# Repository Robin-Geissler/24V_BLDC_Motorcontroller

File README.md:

# 24V BLDC Motorcontroller

This is a motorcontroller to control a 24V BLDC motor. In this project the controller was used to control a Faulhaber 4221 BXT R to power a 2DOF robot. The 6 Step control algorithm is used to control the motor. The motorcontroller implements the following control modes:
* Current Control
* Speed Control
* Position Control
* Torque Control

## Control Structure
A current controller and a speed controller are used as low level controllers for the position and torque controller. Each controlmode can be accessed by the user.

**Current Control** 
Uses currentsensors on the PCB to control the motor current. 

**Speed Control** 
Calculates the speed by analysing the HAL Sector change rate. 

**Position Control**
The position of the geaboxshaft is measured with an AksIM-2 absolute encoder from RLS. The control structure of the position controller looks like this:

**Torque Control**
The torque applied to the gearbox shaft is measured with a TS70a torque sensor from ME-Meßsysteme. The control structure of the torque controller looks like this:

## Comunication Interface
The controller provides an EtherCAT communication interface. Over the interface the controlmode can be set, and PID controlparameters for each controller can be manipulated.

## Hardware
A Microchip ATSAMD51G19A is used as an MCU. It controls a MP6540HA motordriver IC.

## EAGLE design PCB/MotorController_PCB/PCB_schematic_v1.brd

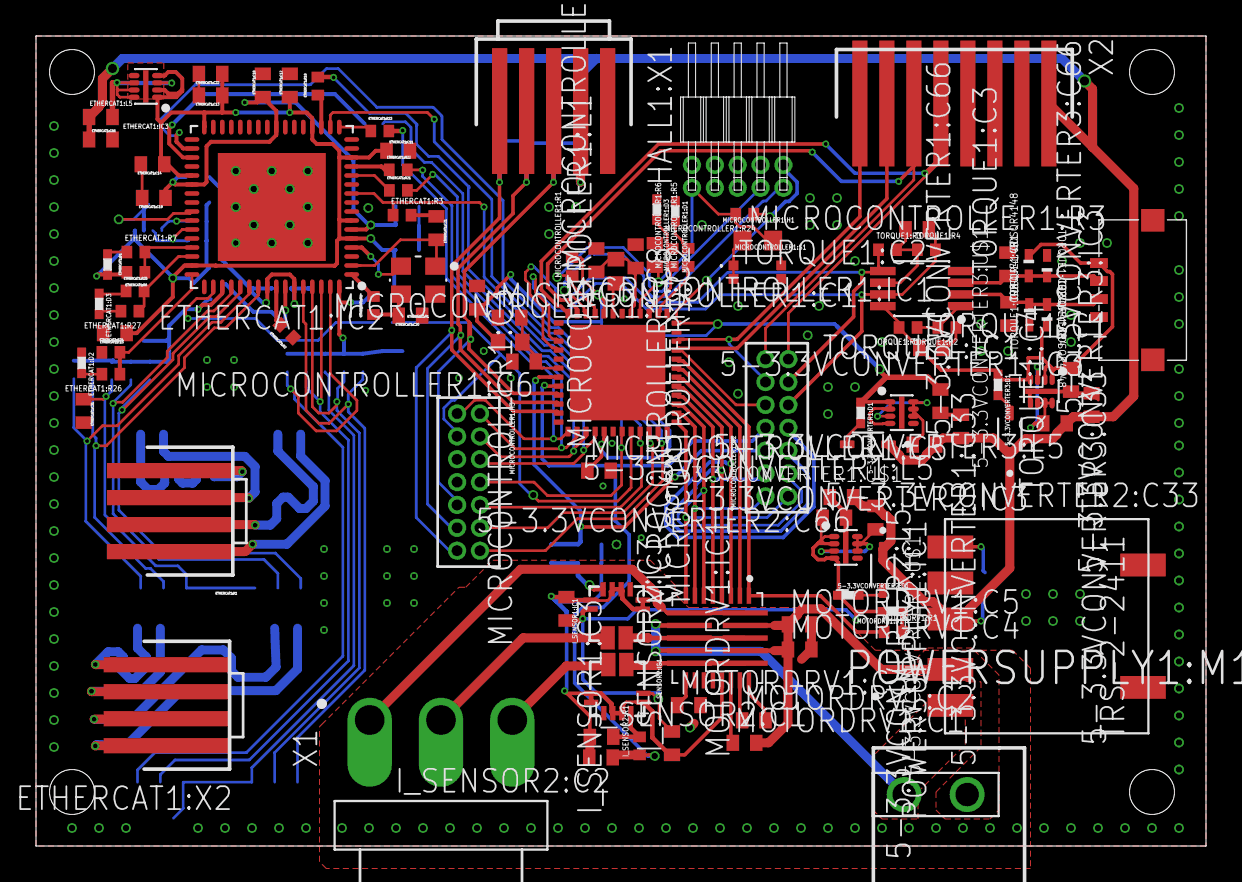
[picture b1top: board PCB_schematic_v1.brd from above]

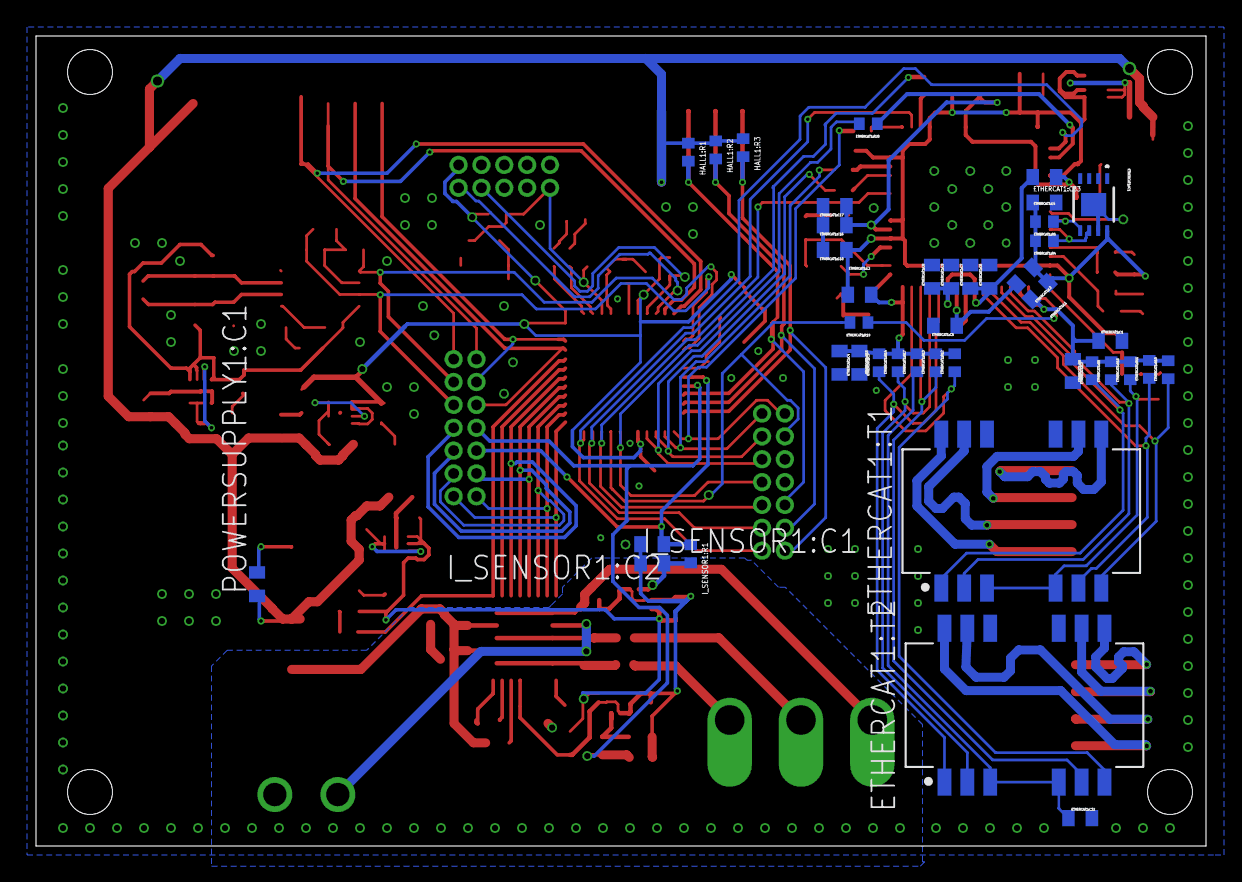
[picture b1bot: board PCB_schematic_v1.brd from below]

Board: 2 copper layers, 65.0 x 45.0 mm, 150 parts (42 on the bottom side), 111 nets.

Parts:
5-3.3VCONVERTER1:C33, 5-3.3VCONVERTER2:C33, 5-3.3VCONVERTER3:C33: GRM155C80J106ME11D; C0402
5-3.3VCONVERTER1:C66, 5-3.3VCONVERTER2:C66, 5-3.3VCONVERTER3:C66: GCM155C71A105KE38D; C0402
5-3.3VCONVERTER1:D1, 5-3.3VCONVERTER2:D1, 5-3.3VCONVERTER3:D1: QBLP595-R; LED0402
5-3.3VCONVERTER1:IC3, 5-3.3VCONVERTER2:IC3, 5-3.3VCONVERTER3:IC3: RP115L331D-E2; SON40P120X160X40-9T30X130N
5-3.3VCONVERTER1:L5, 5-3.3VCONVERTER2:L5, 5-3.3VCONVERTER3:L5: BLM15EG221SH1D; BEAD0402
5-3.3VCONVERTER1:U$1, 5-3.3VCONVERTER2:U$1, 5-3.3VCONVERTER3:U$1: MM3Z3V0B; SODFL2513X100N
ETHERCAT1:C1, ETHERCAT1:C3, ETHERCAT1:C66: GCM155C71A105KE38D; C0402
ETHERCAT1:C2, ETHERCAT1:C4, ETHERCAT1:C5, ETHERCAT1:C7, ETHERCAT1:C9, ETHERCAT1:C10, ETHERCAT1:C11, ETHERCAT1:C12, ETHERCAT1:C13, ETHERCAT1:C14, ETHERCAT1:C15, ETHERCAT1:C18, ETHERCAT1:C19, ETHERCAT1:C22: 100n; C0402
ETHERCAT1:C6, ETHERCAT1:C8, ETHERCAT1:C16: 1u; C0402
ETHERCAT1:C17: 470p; C0402
ETHERCAT1:C20, ETHERCAT1:C21: 18p; C0402
ETHERCAT1:C31, ETHERCAT1:C32: 22n; C0402
ETHERCAT1:C33: GRM155C80J106ME11D; C0402
ETHERCAT1:D1: QBLP595-IG; LED0402
ETHERCAT1:D2: QBLP595-IB; LED0402
ETHERCAT1:D3: QBLP595-O; LED0402
ETHERCAT1:IC1: CAT24C512IGT3HU5; UDFN8
ETHERCAT1:IC2: LAN9253-I/R4X; QFN64-T600
ETHERCAT1:IC3: RP115L331D-E2; SON40P120X160X40-9T30X130N
ETHERCAT1:L1, ETHERCAT1:L2, ETHERCAT1:L3, ETHERCAT1:L4, ETHERCAT1:L5: BLM15EG221SH1D; BEAD0402
ETHERCAT1:R1, ETHERCAT1:R16, ETHERCAT1:R17: RT0402FRE070RL; R0402
ETHERCAT1:R2: 12k1; R0402
ETHERCAT1:R3, ETHERCAT1:R7, ETHERCAT1:R26, ETHERCAT1:R27: RL1206FR-7WL; R0402
ETHERCAT1:R4, ETHERCAT1:R5: 4k7; R0402
ETHERCAT1:R6, ETHERCAT1:R24, ETHERCAT1:R25: 10k; R0402
ETHERCAT1:R8, ETHERCAT1:R9, ETHERCAT1:R10, ETHERCAT1:R11, ETHERCAT1:R12, ETHERCAT1:R13, ETHERCAT1:R14, ETHERCAT1:R15: 49R9; R0402
ETHERCAT1:R18, ETHERCAT1:R19, ETHERCAT1:R20, ETHERCAT1:R21, ETHERCAT1:R22, ETHERCAT1:R23: 100; R0402
ETHERCAT1:T1, ETHERCAT1:T2: 749020100; SOIC127P965X533-16-TRAFO
ETHERCAT1:X1, ETHERCAT1:X2: 87438-0443; 87438-04
ETHERCAT1:Y1: ECX-2236
HALL1:R1, HALL1:R2, HALL1:R3: RT0402BRD0710KL; R0402
HALL1:X1: 87438-0543; 87438-05
I_SENSOR1:C1, I_SENSOR2:C1: GCM155R71E103KA37; C0402
I_SENSOR1:C2, I_SENSOR1:C3, I_SENSOR2:C2, I_SENSOR2:C3: GCM155R71C104JA55; C0402
I_SENSOR1:IC1, I_SENSOR2:IC1: ACS70331EESATR-005B3; QFN12-ES
I_SENSOR1:R1, I_SENSOR2:R1: RT0402FRE07100RL; R0402
MICROCONTROLLER1:C1, MICROCONTROLLER1:C3: GRM155C80J106ME11D; C0402
MICROCONTROLLER1:C2, MICROCONTROLLER1:C5, MICROCONTROLLER1:C6, MICROCONTROLLER1:C7: GCM155R71C104JA55; C0402
MICROCONTROLLER1:C8: GRM155C80J475MEAAD; C0402
MICROCONTROLLER1:D1, MICROCONTROLLER1:D3: QBLP595-AG; LED0402
MICROCONTROLLER1:H1: 20021112-00010T4LF; 20021112-00010
MICROCONTROLLER1:H2, MICROCONTROLLER1:H3: 20021111-00014T1LF; 20021111-00014
MICROCONTROLLER1:IC1: ATSAMD51G19A-MUT; QFN48
MICROCONTROLLER1:L1, MICROCONTROLLER1:L2: BLM18EG601SN1D; BEADC1608X80
MICROCONTROLLER1:R1: RT0402FRE071KL; R0402
MICROCONTROLLER1:R3: RT0603FRE07330RL; R0603
MICROCONTROLLER1:R5, MICROCONTROLLER1:R6, MICROCONTROLLER1:R24: 10k; R0402
MICROCONTROLLER1:S1: USLPT2616CT2TR; USLPT2616CT
MOTORDRV1:C1: GRM155R6YA105KE11D; C0402
MOTORDRV1:C2, MOTORDRV1:C4, MOTORDRV1:C5: GRM155R62A104KE14; C0402
MOTORDRV1:C3: GRM155R61H472KA01D; C0402
MOTORDRV1:D1: QBLP595-R; LED0402
MOTORDRV1:IC1: MP6540HGUP
MOTORDRV1:R1: RT0402BRD0710KL; R0402
POWERSUPPLY1:C1: GRM155R6YA105KE11D; C0402
POWERSUPPLY1:IC1: TRS-2-2411; 7-SMD
POWERSUPPLY1:M1: PST1,3/2-3,5; 1945096
POWERSUPPLY1:U$1: PTDA1,5/2-PH-3,5; 1725107
TORQUE1:C1: GCM155R71C104JA55; C0402
TORQUE1:C2, TORQUE1:C3, TORQUE1:C4: GCM155R71E103KA37; C0402
TORQUE1:CR1, TORQUE1:CR2, TORQUE1:CR3, TORQUE1:CR4: CDSQR4148; 0402/SOD-923F
TORQUE1:IC1: MAX4208AUA+T; USOP8
TORQUE1:R1, TORQUE1:R2: RT0402FRE0710KL; R0402
TORQUE1:R3: RT0402FRE07150RL; R0402
TORQUE1:R4: RT0402FRE07100KL; R0402
TORQUE1:X3: 5037630491
X1: B3PS-VH(LF)(SN)
X2: 87438-0843; 87438-08

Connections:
5-3.3VCONVERTER1:N$1: 5-3.3VCONVERTER1:D1.2, 5-3.3VCONVERTER1:U$1.A
5-3.3VCONVERTER1:VDD: 5-3.3VCONVERTER1:IC3.3, 5-3.3VCONVERTER1:IC3.6, 5-3.3VCONVERTER1:IC3.7, 5-3.3VCONVERTER1:IC3.8, 5-3.3VCONVERTER1:L5.2
5-3.3VCONVERTER2:N$1: 5-3.3VCONVERTER2:D1.2, 5-3.3VCONVERTER2:U$1.A
5-3.3VCONVERTER2:VDD: 5-3.3VCONVERTER2:IC3.3, 5-3.3VCONVERTER2:IC3.6, 5-3.3VCONVERTER2:IC3.7, 5-3.3VCONVERTER2:IC3.8, 5-3.3VCONVERTER2:L5.2
5-3.3VCONVERTER3:N$1: 5-3.3VCONVERTER3:D1.2, 5-3.3VCONVERTER3:U$1.A
5-3.3VCONVERTER3:VDD: 5-3.3VCONVERTER3:IC3.3, 5-3.3VCONVERTER3:IC3.6, 5-3.3VCONVERTER3:IC3.7, 5-3.3VCONVERTER3:IC3.8, 5-3.3VCONVERTER3:L5.2
+3V3_MD: 5-3.3VCONVERTER2:C33.1, 5-3.3VCONVERTER2:D1.1, 5-3.3VCONVERTER2:IC3.1, 5-3.3VCONVERTER2:IC3.2, 5-3.3VCONVERTER2:IC3.4, I_SENSOR1:C3.2, I_SENSOR1:IC1.12, I_SENSOR2:C3.2, I_SENSOR2:IC1.12, MOTORDRV1:D1.2
+3V3_TS: 5-3.3VCONVERTER3:C33.1, 5-3.3VCONVERTER3:D1.1, 5-3.3VCONVERTER3:IC3.1, 5-3.3VCONVERTER3:IC3.2, 5-3.3VCONVERTER3:IC3.4, TORQUE1:C1.1, TORQUE1:CR1.2, TORQUE1:CR4.2, TORQUE1:IC1.8, TORQUE1:R1.2, TORQUE1:X3.4
+3V3_UC: 5-3.3VCONVERTER1:C33.1, 5-3.3VCONVERTER1:D1.1, 5-3.3VCONVERTER1:IC3.1, 5-3.3VCONVERTER1:IC3.2, 5-3.3VCONVERTER1:IC3.4, MICROCONTROLLER1:C3.2, MICROCONTROLLER1:C5.1, MICROCONTROLLER1:H1.1, MICROCONTROLLER1:IC1.17, MICROCONTROLLER1:IC1.36, MICROCONTROLLER1:IC1.44, MICROCONTROLLER1:L2.1, MICROCONTROLLER1:R1.2, MICROCONTROLLER1:R24.1
+5V: 5-3.3VCONVERTER1:C66.1, 5-3.3VCONVERTER1:L5.1, 5-3.3VCONVERTER1:U$1.C, 5-3.3VCONVERTER2:C66.1, 5-3.3VCONVERTER2:L5.1, 5-3.3VCONVERTER2:U$1.C, 5-3.3VCONVERTER3:C66.1, 5-3.3VCONVERTER3:L5.1, 5-3.3VCONVERTER3:U$1.C, ETHERCAT1:C66.1, ETHERCAT1:L5.1, HALL1:R1.1, HALL1:R2.1, HALL1:R3.1, HALL1:X1.2, POWERSUPPLY1:C1.1, POWERSUPPLY1:IC1.3, X2.1
+24V: MOTORDRV1:C1.2, MOTORDRV1:C4.1, MOTORDRV1:C5.1, MOTORDRV1:IC1.23, MOTORDRV1:IC1.25, POWERSUPPLY1:IC1.2, POWERSUPPLY1:M1.2
ADC_TS: MICROCONTROLLER1:H2.9, MICROCONTROLLER1:IC1.3, TORQUE1:C2.1, TORQUE1:IC1.7, TORQUE1:R4.2
AGND: MOTORDRV1:C3.2, MOTORDRV1:C4.2, MOTORDRV1:C5.2, MOTORDRV1:IC1.10, MOTORDRV1:IC1.12, POWERSUPPLY1:IC1.1, POWERSUPPLY1:M1.1
ENA: MICROCONTROLLER1:H2.7, MICROCONTROLLER1:IC1.30, MOTORDRV1:IC1.3
ENB: MICROCONTROLLER1:H2.5, MICROCONTROLLER1:IC1.29, MOTORDRV1:IC1.4
ENC: MICROCONTROLLER1:H2.4, MICROCONTROLLER1:IC1.28, MOTORDRV1:IC1.5
ENCODER_SPI_MISO: MICROCONTROLLER1:H2.10, MICROCONTROLLER1:IC1.33, X2.7
ENCODER_SPI_MOSI: MICROCONTROLLER1:H2.12, MICROCONTROLLER1:IC1.34, X2.8
ENCODER_SPI_NCS: MICROCONTROLLER1:H2.14, MICROCONTROLLER1:IC1.47, X2.6
ENCODER_SPI_SCK: MICROCONTROLLER1:H2.13, MICROCONTROLLER1:IC1.48, X2.5
ETHERCAT1:#MISO: ETHERCAT1:IC2.13, ETHERCAT1:R22.1
ETHERCAT1:#MOSI: ETHERCAT1:IC2.17, ETHERCAT1:R23.1
ETHERCAT1:#SCK: ETHERCAT1:IC2.19, ETHERCAT1:R18.1
ETHERCAT1:#SCS#: ETHERCAT1:IC2.50, ETHERCAT1:R19.1
ETHERCAT1:#SQI2: ETHERCAT1:IC2.12, ETHERCAT1:R21.1
ETHERCAT1:#SQI3: ETHERCAT1:IC2.35, ETHERCAT1:R20.1
ETHERCAT1:+3V3: ETHERCAT1:C10.1, ETHERCAT1:C11.1, ETHERCAT1:C12.1, ETHERCAT1:C13.1, ETHERCAT1:C14.1, ETHERCAT1:C15.1, ETHERCAT1:C22.1, ETHERCAT1:C33.1, ETHERCAT1:D1.2, ETHERCAT1:IC1.8, ETHERCAT1:IC2.5, ETHERCAT1:IC2.7, ETHERCAT1:IC2.14, ETHERCAT1:IC2.20, ETHERCAT1:IC2.32, ETHERCAT1:IC2.37, ETHERCAT1:IC2.47, ETHERCAT1:IC3.1, ETHERCAT1:IC3.2, ETHERCAT1:IC3.4, ETHERCAT1:L1.1, ETHERCAT1:L2.1, ETHERCAT1:L3.1, ETHERCAT1:R4.2, ETHERCAT1:R5.2, ETHERCAT1:R6.2
ETHERCAT1:CT1: ETHERCAT1:C31.1, ETHERCAT1:R16.1, ETHERCAT1:T1.3, ETHERCAT1:T1.6
ETHERCAT1:CT2: ETHERCAT1:C32.1, ETHERCAT1:R17.1, ETHERCAT1:T2.3, ETHERCAT1:T2.6
ETHERCAT1:GPIO0: ETHERCAT1:IC2.48, ETHERCAT1:R24.2, ETHERCAT1:R26.1
ETHERCAT1:GPIO1: ETHERCAT1:IC2.46, ETHERCAT1:R25.2, ETHERCAT1:R27.1
ETHERCAT1:GPIO2: ETHERCAT1:IC2.45, ETHERCAT1:R6.1, ETHERCAT1:R7.2
ETHERCAT1:I2C_SCL: ETHERCAT1:IC1.6, ETHERCAT1:IC2.43, ETHERCAT1:R4.1
ETHERCAT1:I2C_SDA: ETHERCAT1:IC1.5, ETHERCAT1:IC2.42, ETHERCAT1:R5.1
ETHERCAT1:IN_RX_N: ETHERCAT1:T1.9, ETHERCAT1:X1.4
ETHERCAT1:IN_RX_P: ETHERCAT1:T1.10, ETHERCAT1:X1.3
ETHERCAT1:IN_TX_N: ETHERCAT1:T1.15, ETHERCAT1:X1.2
ETHERCAT1:IN_TX_P: ETHERCAT1:T1.16, ETHERCAT1:X1.1
ETHERCAT1:N$1: ETHERCAT1:D2.2, ETHERCAT1:R26.2
ETHERCAT1:N$2: ETHERCAT1:D3.2, ETHERCAT1:R27.2
ETHERCAT1:N$3: ETHERCAT1:IC3.3, ETHERCAT1:IC3.6, ETHERCAT1:IC3.7, ETHERCAT1:IC3.8, ETHERCAT1:L5.2
ETHERCAT1:N$15: ETHERCAT1:D1.1, ETHERCAT1:R7.1
ETHERCAT1:OSCI: ETHERCAT1:IC2.1, ETHERCAT1:R1.2
ETHERCAT1:OSCI1: ETHERCAT1:C20.2, ETHERCAT1:R1.1, ETHERCAT1:Y1.3
ETHERCAT1:OSCO: ETHERCAT1:C21.2, ETHERCAT1:IC2.2, ETHERCAT1:Y1.1
ETHERCAT1:OUT_RX_N: ETHERCAT1:T2.9, ETHERCAT1:X2.4
ETHERCAT1:OUT_RX_P: ETHERCAT1:T2.10, ETHERCAT1:X2.3
ETHERCAT1:OUT_TX_N: ETHERCAT1:T2.15, ETHERCAT1:X2.2
ETHERCAT1:OUT_TX_P: ETHERCAT1:T2.16, ETHERCAT1:X2.1
ETHERCAT1:RBIAS: ETHERCAT1:IC2.57, ETHERCAT1:R2.2
ETHERCAT1:RXA_N: ETHERCAT1:IC2.54, ETHERCAT1:R10.1, ETHERCAT1:T1.8
ETHERCAT1:RXA_P: ETHERCAT1:IC2.55, ETHERCAT1:R11.1, ETHERCAT1:T1.7
ETHERCAT1:RXB_N: ETHERCAT1:IC2.61, ETHERCAT1:R14.1, ETHERCAT1:T2.2
ETHERCAT1:RXB_P: ETHERCAT1:IC2.60, ETHERCAT1:R15.1, ETHERCAT1:T2.1
ETHERCAT1:TXA_N: ETHERCAT1:IC2.52, ETHERCAT1:R8.1, ETHERCAT1:T1.2
ETHERCAT1:TXA_P: ETHERCAT1:IC2.53, ETHERCAT1:R9.1, ETHERCAT1:T1.1
ETHERCAT1:TXB_N: ETHERCAT1:IC2.63, ETHERCAT1:R12.1, ETHERCAT1:T2.8
ETHERCAT1:TXB_P: ETHERCAT1:IC2.62, ETHERCAT1:R13.1, ETHERCAT1:T2.7
ETHERCAT1:VDD: ETHERCAT1:C16.1, ETHERCAT1:C17.1, ETHERCAT1:C18.1, ETHERCAT1:C19.1, ETHERCAT1:IC2.6, ETHERCAT1:IC2.24, ETHERCAT1:IC2.38, ETHERCAT1:L4.1
ETHERCAT1:VDD12TX: ETHERCAT1:C6.1, ETHERCAT1:C7.1, ETHERCAT1:C8.1, ETHERCAT1:C9.1, ETHERCAT1:IC2.56, ETHERCAT1:IC2.59, ETHERCAT1:L4.2
ETHERCAT1:VDD33BIAS: ETHERCAT1:C5.1, ETHERCAT1:IC2.58, ETHERCAT1:L3.2
ETHERCAT1:VDD33TXRX1: ETHERCAT1:C1.1, ETHERCAT1:C2.1, ETHERCAT1:IC2.51, ETHERCAT1:L1.2, ETHERCAT1:R8.2, ETHERCAT1:R9.2, ETHERCAT1:R10.2, ETHERCAT1:R11.2, ETHERCAT1:R16.2
ETHERCAT1:VDD33TXRX2: ETHERCAT1:C3.1, ETHERCAT1:C4.1, ETHERCAT1:IC2.64, ETHERCAT1:L2.2, ETHERCAT1:R12.2, ETHERCAT1:R13.2, ETHERCAT1:R14.2, ETHERCAT1:R15.2, ETHERCAT1:R17.2
ETH_CS: ETHERCAT1:R19.2, MICROCONTROLLER1:H3.3, MICROCONTROLLER1:IC1.20
ETH_IO2: ETHERCAT1:R21.2, MICROCONTROLLER1:H3.4, MICROCONTROLLER1:IC1.15
ETH_IO3: ETHERCAT1:R20.2, MICROCONTROLLER1:H3.6, MICROCONTROLLER1:IC1.16
ETH_MISO: ETHERCAT1:R22.2, MICROCONTROLLER1:H3.2, MICROCONTROLLER1:IC1.14
ETH_MOSI: ETHERCAT1:R23.2, MICROCONTROLLER1:H3.1, MICROCONTROLLER1:IC1.13
ETH_SCK: ETHERCAT1:R18.2, MICROCONTROLLER1:H3.8, MICROCONTROLLER1:IC1.19
GND: 5-3.3VCONVERTER1:C33.2, 5-3.3VCONVERTER1:C66.2, 5-3.3VCONVERTER1:IC3.5, 5-3.3VCONVERTER1:IC3.9, 5-3.3VCONVERTER2:C33.2, 5-3.3VCONVERTER2:C66.2, 5-3.3VCONVERTER2:IC3.5, 5-3.3VCONVERTER2:IC3.9, 5-3.3VCONVERTER3:C33.2, 5-3.3VCONVERTER3:C66.2, 5-3.3VCONVERTER3:IC3.5, 5-3.3VCONVERTER3:IC3.9, ETHERCAT1:C1.2, ETHERCAT1:C2.2, ETHERCAT1:C3.2, ETHERCAT1:C4.2, ETHERCAT1:C5.2, ETHERCAT1:C6.2, ETHERCAT1:C7.2, ETHERCAT1:C8.2, ETHERCAT1:C9.2, ETHERCAT1:C10.2, ETHERCAT1:C11.2, ETHERCAT1:C12.2, ETHERCAT1:C13.2, ETHERCAT1:C14.2, ETHERCAT1:C15.2, ETHERCAT1:C16.2, ETHERCAT1:C17.2, ETHERCAT1:C18.2, ETHERCAT1:C19.2, ETHERCAT1:C20.1, ETHERCAT1:C21.1, ETHERCAT1:C22.2, ETHERCAT1:C31.2, ETHERCAT1:C32.2, ETHERCAT1:C33.2, ETHERCAT1:C66.2, ETHERCAT1:D2.1, ETHERCAT1:D3.1, ETHERCAT1:IC1.1, ETHERCAT1:IC1.2, ETHERCAT1:IC1.3, ETHERCAT1:IC1.4, ETHERCAT1:IC1.7, ETHERCAT1:IC1.9, ETHERCAT1:IC2.4, ETHERCAT1:IC2.8, ETHERCAT1:IC2.9, ETHERCAT1:IC2.41, ETHERCAT1:IC2.65, ETHERCAT1:IC3.5, ETHERCAT1:IC3.9, ETHERCAT1:R2.1, ETHERCAT1:R3.2, ETHERCAT1:R24.1, ETHERCAT1:R25.1, ETHERCAT1:Y1.2, ETHERCAT1:Y1.4, HALL1:X1.1, I_SENSOR1:C1.1, I_SENSOR1:C2.2, I_SENSOR1:C3.1, I_SENSOR1:IC1.5, I_SENSOR1:IC1.6, I_SENSOR1:IC1.8, I_SENSOR1:IC1.9, I_SENSOR1:IC1.11, I_SENSOR2:C1.1, I_SENSOR2:C2.2, I_SENSOR2:C3.1, I_SENSOR2:IC1.5, I_SENSOR2:IC1.6, I_SENSOR2:IC1.8, I_SENSOR2:IC1.9, I_SENSOR2:IC1.11, MICROCONTROLLER1:C1.1, MICROCONTROLLER1:C2.1, MICROCONTROLLER1:C3.1, MICROCONTROLLER1:C5.2, MICROCONTROLLER1:C6.2, MICROCONTROLLER1:C7.2, MICROCONTROLLER1:C8.1, MICROCONTROLLER1:D1.1, MICROCONTROLLER1:D3.1, MICROCONTROLLER1:H1.3, MICROCONTROLLER1:H1.5, MICROCONTROLLER1:H3.5, MICROCONTROLLER1:H3.7, MICROCONTROLLER1:IC1.5, MICROCONTROLLER1:IC1.18, MICROCONTROLLER1:IC1.35, MICROCONTROLLER1:IC1.42, MICROCONTROLLER1:S1.2, MICROCONTROLLER1:S1.4, MOTORDRV1:IC1.18, POWERSUPPLY1:C1.2, POWERSUPPLY1:IC1.5, TORQUE1:C1.2, TORQUE1:C3.2, TORQUE1:C4.2, TORQUE1:CR2.1, TORQUE1:CR3.1, TORQUE1:IC1.4, TORQUE1:R2.1, TORQUE1:X3.1, X2.2
HALL_A: HALL1:R3.2, HALL1:X1.5, MICROCONTROLLER1:H3.13, MICROCONTROLLER1:IC1.11
HALL_B: HALL1:R2.2, HALL1:X1.4, MICROCONTROLLER1:H3.11, MICROCONTROLLER1:IC1.10
HALL_C: HALL1:R1.2, HALL1:X1.3, MICROCONTROLLER1:H3.9, MICROCONTROLLER1:IC1.9
I2-: I_SENSOR1:C2.1, I_SENSOR1:R1.1, MICROCONTROLLER1:H2.6, MICROCONTROLLER1:IC1.7
I3+: I_SENSOR2:C2.1, I_SENSOR2:R1.1, MICROCONTROLLER1:H2.8, MICROCONTROLLER1:IC1.8
I_SENSOR1:VI: I_SENSOR1:C1.2, I_SENSOR1:IC1.10, I_SENSOR1:R1.2
I_SENSOR2:VI: I_SENSOR2:C1.2, I_SENSOR2:IC1.10, I_SENSOR2:R1.2
MICROCONTROLLER1:LED_PA27: MICROCONTROLLER1:IC1.39, MICROCONTROLLER1:R6.1
MICROCONTROLLER1:LED_PB23: MICROCONTROLLER1:IC1.38, MICROCONTROLLER1:R5.1
MICROCONTROLLER1:N$1: MICROCONTROLLER1:R3.1, MICROCONTROLLER1:S1.1, MICROCONTROLLER1:S1.3
MICROCONTROLLER1:N$2: MICROCONTROLLER1:D3.2, MICROCONTROLLER1:R6.2
MICROCONTROLLER1:N$4: MICROCONTROLLER1:D1.2, MICROCONTROLLER1:R5.2
MICROCONTROLLER1:NRESET: MICROCONTROLLER1:C2.2, MICROCONTROLLER1:H1.10, MICROCONTROLLER1:IC1.40, MICROCONTROLLER1:R3.2, MICROCONTROLLER1:R24.2
MICROCONTROLLER1:SWCLK: MICROCONTROLLER1:H1.4, MICROCONTROLLER1:IC1.45, MICROCONTROLLER1:R1.1
MICROCONTROLLER1:SWDIO: MICROCONTROLLER1:H1.2, MICROCONTROLLER1:IC1.46
MICROCONTROLLER1:VDDANA: MICROCONTROLLER1:C1.2, MICROCONTROLLER1:C6.1, MICROCONTROLLER1:IC1.6, MICROCONTROLLER1:L2.2
MICROCONTROLLER1:VDDCORE: MICROCONTROLLER1:C7.1, MICROCONTROLLER1:C8.2, MICROCONTROLLER1:IC1.41, MICROCONTROLLER1:L1.2
MICROCONTROLLER1:VSW: MICROCONTROLLER1:IC1.43, MICROCONTROLLER1:L1.1
MOTORDRV1:CP1: MOTORDRV1:C2.1, MOTORDRV1:IC1.20
MOTORDRV1:CP2: MOTORDRV1:C2.2, MOTORDRV1:IC1.21
MOTORDRV1:N$1: MOTORDRV1:D1.1, MOTORDRV1:R1.2
MOTORDRV1:VCP: MOTORDRV1:C1.1, MOTORDRV1:IC1.19
MOTORDRV1:VG: MOTORDRV1:C3.1, MOTORDRV1:IC1.14
NFAULT: MICROCONTROLLER1:IC1.32, MOTORDRV1:IC1.1, MOTORDRV1:R1.1
NSLEEP: MICROCONTROLLER1:IC1.31, MOTORDRV1:IC1.2
OUT1: MOTORDRV1:IC1.9, MOTORDRV1:IC1.26, X1.1
OUT2: I_SENSOR1:IC1.1,2, X1.2
OUT3: I_SENSOR2:IC1.3,4, X1.3
PWMA: MICROCONTROLLER1:H2.3, MICROCONTROLLER1:IC1.27, MOTORDRV1:IC1.6
PWMB: MICROCONTROLLER1:H2.2, MICROCONTROLLER1:IC1.26, MOTORDRV1:IC1.7
PWMC: MICROCONTROLLER1:H2.1, MICROCONTROLLER1:IC1.25, MOTORDRV1:IC1.8
SB: I_SENSOR1:IC1.3,4, MOTORDRV1:IC1.11, MOTORDRV1:IC1.24
SC: I_SENSOR2:IC1.1,2, MOTORDRV1:IC1.13, MOTORDRV1:IC1.22
SYNC0: ETHERCAT1:IC2.34, MICROCONTROLLER1:H3.14, MICROCONTROLLER1:IC1.23
SYNC1: ETHERCAT1:IC2.18, MICROCONTROLLER1:H3.12, MICROCONTROLLER1:IC1.22
TORQUE1:+VO_B: TORQUE1:C3.1, TORQUE1:CR1.1, TORQUE1:CR2.2, TORQUE1:IC1.3, TORQUE1:X3.3
TORQUE1:-VO_B: TORQUE1:C4.1, TORQUE1:CR3.2, TORQUE1:CR4.1, TORQUE1:IC1.2, TORQUE1:X3.2
TORQUE1:VI_REF: TORQUE1:IC1.1, TORQUE1:R1.1, TORQUE1:R2.2
TORQUE1:V_FB: TORQUE1:C2.2, TORQUE1:IC1.6, TORQUE1:R3.2, TORQUE1:R4.1
VREF_TS: MICROCONTROLLER1:H2.11, MICROCONTROLLER1:IC1.4, TORQUE1:IC1.5, TORQUE1:R3.1
WAIT_ACK: ETHERCAT1:IC2.10, ETHERCAT1:R3.1, MICROCONTROLLER1:H3.10, MICROCONTROLLER1:IC1.21

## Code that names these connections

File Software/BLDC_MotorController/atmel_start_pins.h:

/*
 * Code generated from Atmel Start.
 *
 * This file will be overwritten when reconfiguring your Atmel Start project.
 * Please copy examples or other code you want to keep to a separate file
 * to avoid losing it when reconfiguring.
 */
#ifndef ATMEL_START_PINS_H_INCLUDED
#define ATMEL_START_PINS_H_INCLUDED

#include <hal_gpio.h>

// SAMD51 has 14 pin functions

#define GPIO_PIN_FUNCTION_A 0
#define GPIO_PIN_FUNCTION_B 1
#define GPIO_PIN_FUNCTION_C 2
#define GPIO_PIN_FUNCTION_D 3
#define GPIO_PIN_FUNCTION_E 4
#define GPIO_PIN_FUNCTION_F 5
#define GPIO_PIN_FUNCTION_G 6
#define GPIO_PIN_FUNCTION_H 7
#define GPIO_PIN_FUNCTION_I 8
#define GPIO_PIN_FUNCTION_J 9
#define GPIO_PIN_FUNCTION_K 10
#define GPIO_PIN_FUNCTION_L 11
#define GPIO_PIN_FUNCTION_M 12
#define GPIO_PIN_FUNCTION_N 13

#define ADC_PLUS GPIO(GPIO_PORTA, 2)
#define ADC_MINUS GPIO(GPIO_PORTA, 3)
#define HALL_C GPIO(GPIO_PORTA, 4)
#define HALL_B GPIO(GPIO_PORTA, 5)
#define HALL_A GPIO(GPIO_PORTA, 6)
#define HALL_OUT GPIO(GPIO_PORTA, 7)
#define ECAT_SPI_DATA0 GPIO(GPIO_PORTA, 8)
#define ECAT_SPI_DATA1 GPIO(GPIO_PORTA, 9)
#define ECAT_SPI_DATA2 GPIO(GPIO_PORTA, 10)
#define ECAT_SPI_DATA3 GPIO(GPIO_PORTA, 11)
#define ECAT_GPIO1 GPIO(GPIO_PORTA, 12)
#define ECAT_GPIO2 GPIO(GPIO_PORTA, 13)
#define ECAT_GPIO3 GPIO(GPIO_PORTA, 14)
#define ECAT_GPIO4 GPIO(GPIO_PORTA, 15)
#define PWM_C GPIO(GPIO_PORTA, 16)
#define PWM_B GPIO(GPIO_PORTA, 17)
#define PWM_A GPIO(GPIO_PORTA, 18)
#define EN_C GPIO(GPIO_PORTA, 19)
#define EN_B GPIO(GPIO_PORTA, 20)
#define EN_A GPIO(GPIO_PORTA, 21)
#define NSLEEP GPIO(GPIO_PORTA, 22)
#define NFAULT GPIO(GPIO_PORTA, 23)
#define ENCODER_SPI_MISO GPIO(GPIO_PORTA, 24)
#define ENCODER_SPI_MOSI GPIO(GPIO_PORTA, 25)
#define STATUS_LED1 GPIO(GPIO_PORTA, 27)
#define ENCODER_SPI_NCS GPIO(GPIO_PORTB, 2)
#define ENCODER_SPI_SCK GPIO(GPIO_PORTB, 3)
#define ADC_A GPIO(GPIO_PORTB, 8)
#define ADC_B GPIO(GPIO_PORTB, 9)
#define ECAT_SPI_SCK GPIO(GPIO_PORTB, 10)
#define ECAT_SPI_CS GPIO(GPIO_PORTB, 11)
#define STATUS_LED2 GPIO(GPIO_PORTB, 23)

#endif // ATMEL_START_PINS_H_INCLUDED

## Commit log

2023-06-22 manual import from gitlab
